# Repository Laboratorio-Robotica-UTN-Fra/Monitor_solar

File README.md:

# Monitor Solar

Proyecto para mostrar los valores de tension y corriente de un sistema solar

## Folder Structure

- `code/` - Archivos de codigo para esp8266.
- `Componentes/` - Documentacion y archivos de simbolos para kicad.
- `img/` - Imagenes del proyecto
- `README.md` - Explicacion del proyecto.

## Getting Started

1. Clone the repository:
    ```bash
    git clone https://github.com/yourusername/Monitor_solar.git
    ```
2. Follow instructions in `docs/` to set up and run the project.

## License

See `LICENSE` for details.

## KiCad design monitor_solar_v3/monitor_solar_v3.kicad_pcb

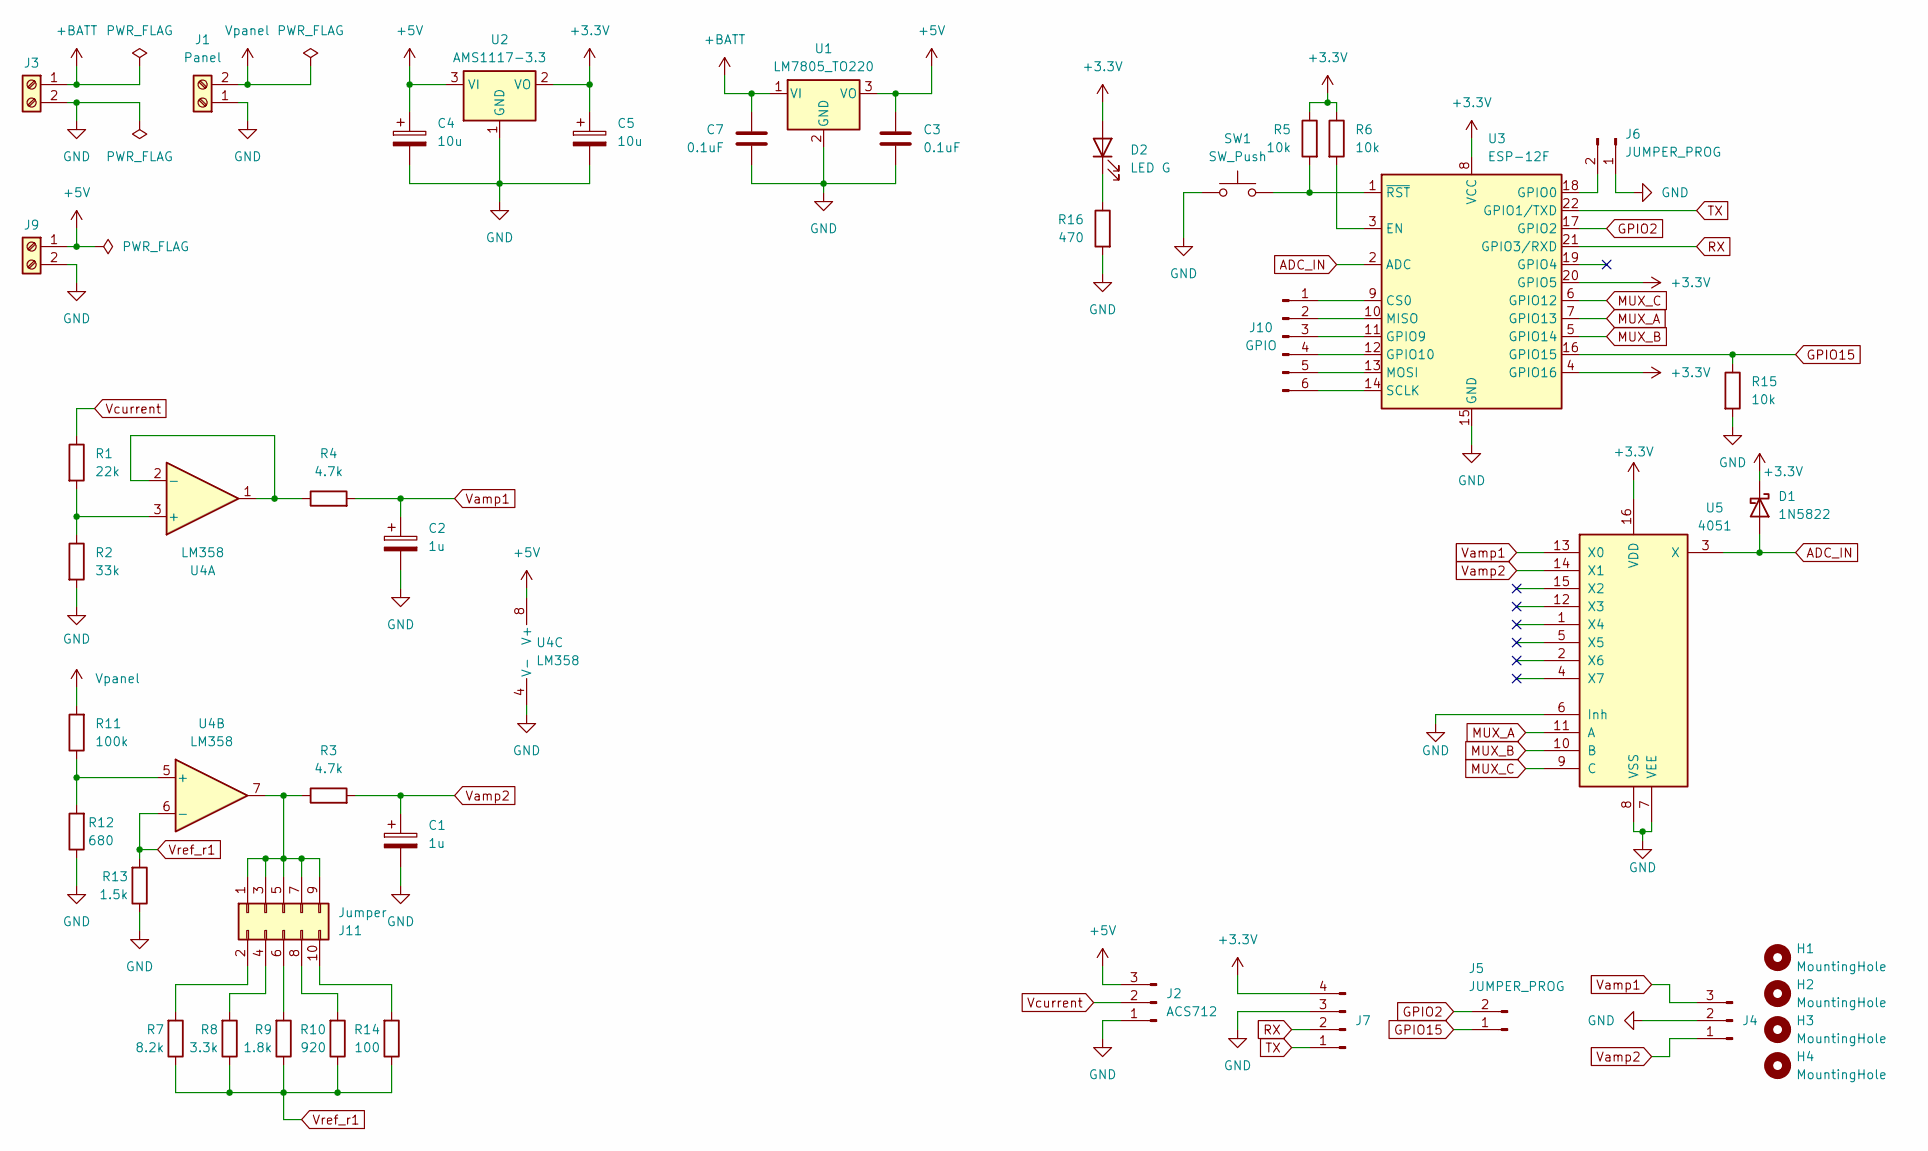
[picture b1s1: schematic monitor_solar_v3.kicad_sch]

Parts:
C1, C2: 1u; CP_Radial_D5.0mm_P2.50mm
C3, C7: 0.1uF; C_Disc_D3.0mm_W2.0mm_P2.50mm
C4, C5: 10u; CP_Radial_D5.0mm_P2.50mm
D1: 1N5822; D_DO-201AD_P15.24mm_Horizontal
D2: LED G; LED_D3.0mm
H1, H2, H3, H4: MountingHole; MountingHole_3.2mm_M3
J1: Panel; TerminalBlock_Phoenix_MKDS-1,5-2-5.08_1x02_P5.08mm_Horizont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
J2: ACS712; PinHeader_1x03_P2.54mm_Vertical
J3: Battery; TerminalBlock_Phoenix_MKDS-1,5-2-5.08_1x02_P5.08mm_Horizont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
J4: AMP_OUT; PinHeader_1x03_P2.54mm_Vertical
J5, J6: JUMPER_PROG; PinHeader_1x02_P2.54mm_Vertical
J7: PROGRAM; PinHeader_1x04_P2.54mm_Vertical
J9: Reg 5V; TerminalBlock_Phoenix_MKDS-1,5-2-5.08_1x02_P5.08mm_Horizont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
J10: GPIO; PinHeader_1x06_P2.54mm_Vertical
J11: Jumper; PinHeader_2x05_P2.54mm_Vertical
R1: 22k; R_Axial_DIN0207_L6.3mm_D2.5mm_P10.16mm_Horizontal
R2: 33k; R_Axial_DIN0207_L6.3mm_D2.5mm_P10.16mm_Horizontal
R3: 4.7k; R_Axial_DIN0207_L6.3mm_D2.5mm_P10.16mm_Horizontal
R4: 4.7k; R_Axial_DIN0207_L6.3mm_D2.5mm_P7.62mm_Horizontal
R5, R6, R15: 10k; R_Axial_DIN0207_L6.3mm_D2.5mm_P10.16mm_Horizontal
R7: 8.2k; R_Axial_DIN0207_L6.3mm_D2.5mm_P7.62mm_Horizontal
R8: 3.3k; R_Axial_DIN0207_L6.3mm_D2.5mm_P7.62mm_Horizontal
R9: 1.8k; R_Axial_DIN0207_L6.3mm_D2.5mm_P7.62mm_Horizontal
R10: 920; R_Axial_DIN0207_L6.3mm_D2.5mm_P7.62mm_Horizontal
R11: 100k; R_Axial_DIN0207_L6.3mm_D2.5mm_P10.16mm_Horizontal
R12: 680; R_Axial_DIN0207_L6.3mm_D2.5mm_P10.16mm_Horizontal
R13: 1.5k; R_Axial_DIN0207_L6.3mm_D2.5mm_P10.16mm_Horizontal
R14: 100; R_Axial_DIN0207_L6.3mm_D2.5mm_P7.62mm_Horizontal
R16: 470; R_Axial_DIN0207_L6.3mm_D2.5mm_P10.16mm_Horizontal
SW1: SW_Push; SW_PUSH_6mm
U1: LM7805_TO220; TO-220-3_Vertical
U2: AMS1117-3.3; SOT-223-3_TabPin2
U3: ESP-12F; ESP-12E
U4: LM358; DIP-8_W10.16mm_LongPads
U5: 4051; DIP-16_W7.62mm_Socket_LongPads

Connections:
+3.3V: C5.1, D1.1 (K), D2.2 (A), J7.4, R5.1, R6.1, U2.2 (VO), U3.4 (GPIO16), U3.8 (VCC), U3.20 (GPIO5), U5.16 (VDD)
+5V: C3.1, C4.1, J2.3, J9.1, U1.3 (VO), U2.3 (VI), U4.8 (V+)
+BATT: C7.1, J3.1, U1.1 (VI)
ADC_IN: D1.2 (A), U3.2 (ADC), U5.3 (X)
GND: C1.2, C2.2, C3.2, C4.2, C5.2, C7.2, J1.1, J2.1, J3.2, J4.2, J6.1, J7.3, J9.2, R2.2, R12.1, R13.1, R15.2, R16.2, SW1.1, U1.2 (GND), U2.1 (GND), U3.15 (GND), U4.4 (V-), U5.6 (Inh), U5.7 (VEE), U5.8 (VSS)
GPIO2: J5.2, U3.17 (GPIO2)
GPIO15: J5.1, R15.1, U3.16 (GPIO15)
MUX_A: U3.7 (GPIO13), U5.11 (A)
MUX_B: U3.5 (GPIO14), U5.10 (B)
MUX_C: U3.6 (GPIO12), U5.9 (C)
unnamed: D2.1 (K), R16.1
unnamed: J6.2, U3.18 (GPIO0)
unnamed: J10.1, U3.9 (CS0)
unnamed: J10.2, U3.10 (MISO)
unnamed: J10.3, U3.11 (GPIO9)
unnamed: J10.4, U3.12 (GPIO10)
unnamed: J10.5, U3.13 (MOSI)
unnamed: J10.6, U3.14 (SCLK)
unnamed: J11.1, J11.3, J11.5, J11.7, J11.9, R3.1, U4.7
unnamed: J11.2, R7.2
unnamed: J11.4, R8.2
unnamed: J11.6, R9.2
unnamed: J11.8, R10.2
unnamed: J11.10, R14.2
unnamed: R6.2, U3.3 (EN)
unnamed: R5.2, SW1.2, U3.1 (~RST)
unnamed: R1.2, R2.1, U4.3 (+)
unnamed: R4.1, U4.1, U4.2 (-)
unnamed: R11.1, R12.2, U4.5 (+)
RX: J7.2, U3.21 (GPIO3/RXD)
TX: J7.1, U3.22 (GPIO1/TXD)
Vamp1: C2.1, J4.3, R4.2, U5.13 (X0)
Vamp2: C1.1, J4.1, R3.2, U5.14 (X1)
Vcurrent: J2.2, R1.1
Vpanel: J1.2, R11.2
Vref_r1: R7.1, R8.1, R9.1, R10.1, R13.2, R14.1, U4.6 (-)

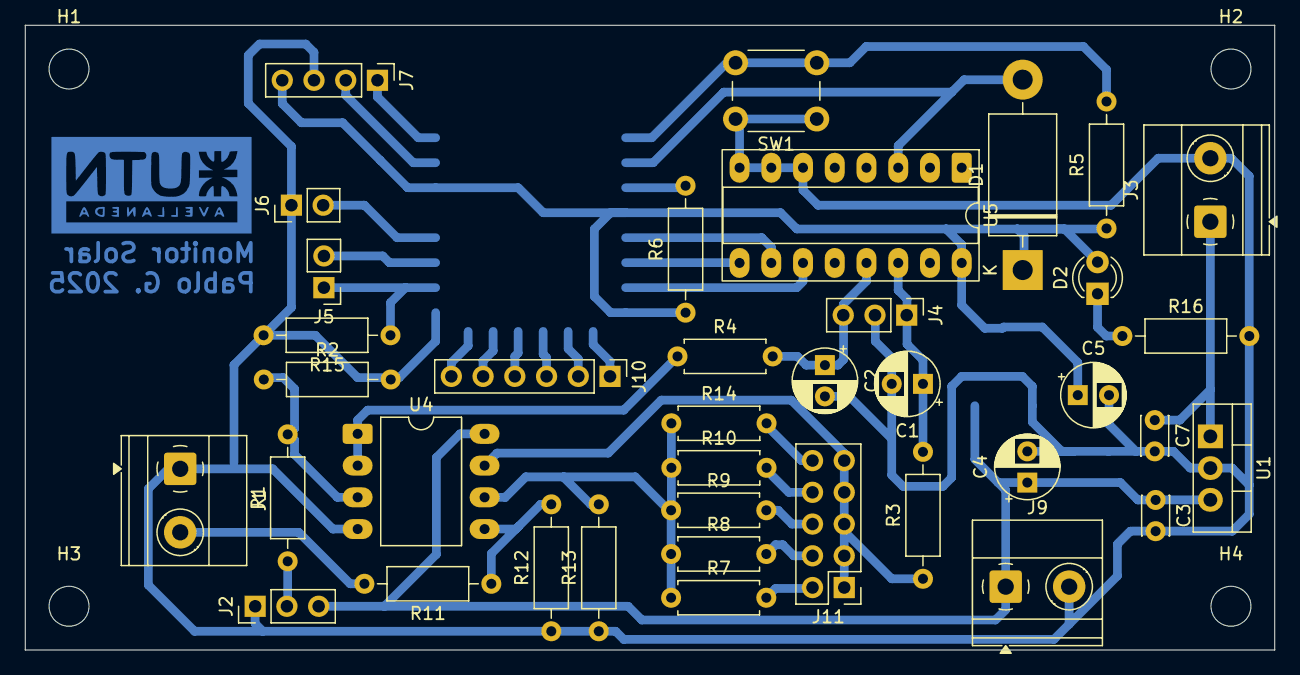
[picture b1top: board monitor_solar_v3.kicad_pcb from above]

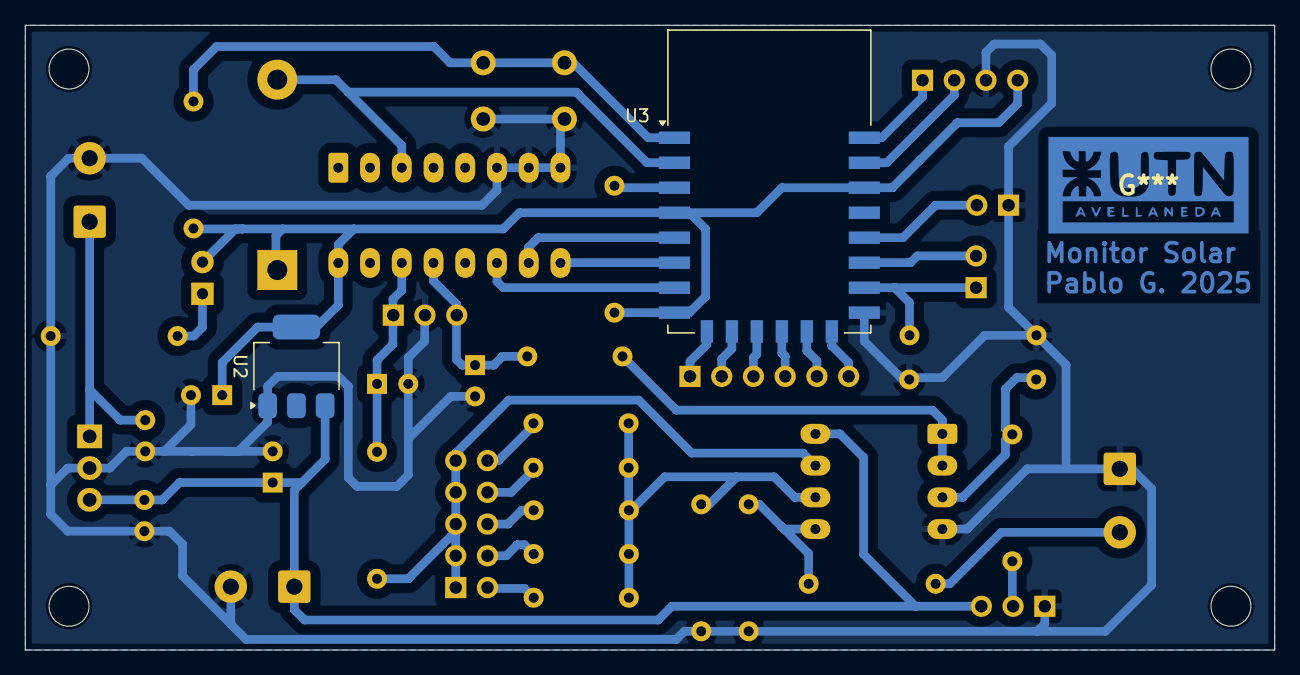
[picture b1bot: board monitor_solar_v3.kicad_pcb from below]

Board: 2 copper layers, 100.0 x 50.0 mm, 44 parts (2 on the bottom side), 36 nets.

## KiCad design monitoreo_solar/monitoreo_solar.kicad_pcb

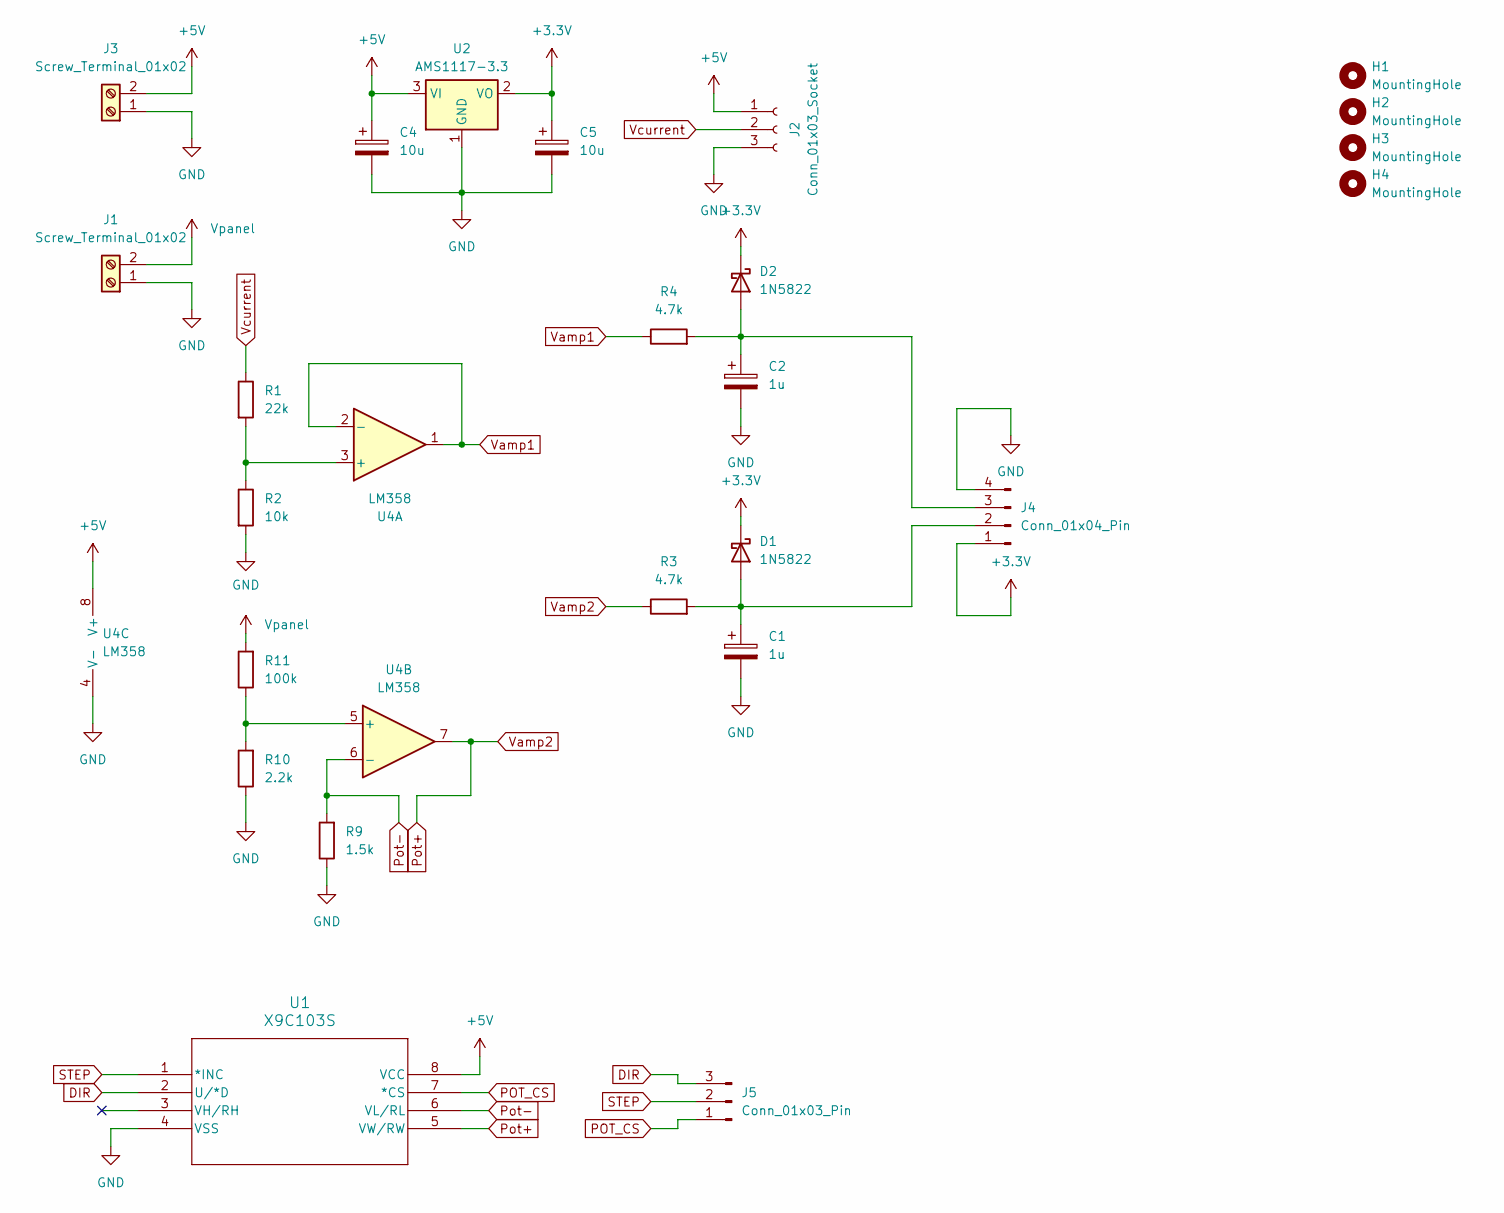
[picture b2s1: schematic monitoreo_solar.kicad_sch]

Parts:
C1, C2: 1u; CP_Radial_D5.0mm_P2.50mm
C4, C5: 10u; CP_Radial_D5.0mm_P2.50mm
D1, D2: 1N5822; D_DO-201AD_P15.24mm_Horizontal
H1, H2, H3, H4: MountingHole; MountingHole_3.2mm_M3
J1, J3: Screw_Terminal_01x02; TerminalBlock_Phoenix_MKDS-1,5-2_1x02_P5.00mm_Horizontal
J2: Conn_01x03_Socket; PinHeader_1x03_P2.54mm_Vertical
J4: Conn_01x04_Pin; PinHeader_1x04_P2.54mm_Vertical
J5: Conn_01x03_Pin; PinHeader_1x03_P2.54mm_Vertical
R1: 22k; R_Axial_DIN0207_L6.3mm_D2.5mm_P10.16mm_Horizontal
R2: 10k; R_Axial_DIN0207_L6.3mm_D2.5mm_P10.16mm_Horizontal
R3, R4: 4.7k; R_Axial_DIN0207_L6.3mm_D2.5mm_P10.16mm_Horizontal
R9: 1.5k; R_Axial_DIN0207_L6.3mm_D2.5mm_P10.16mm_Horizontal
R10: 2.2k; R_Axial_DIN0207_L6.3mm_D2.5mm_P10.16mm_Horizontal
R11: 100k; R_Axial_DIN0207_L6.3mm_D2.5mm_P10.16mm_Horizontal
U1: X9C103S; SOIC8_3P9116X4P9022_INR
U2: AMS1117-3.3; TO-220-3_Vertical
U4: LM358; DIP-8_W10.16mm_LongPads

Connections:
+3.3V: C5.1, D1.1 (K), D2.1 (K), J4.1, U2.2 (VO)
+5V: C4.1, J2.1, J3.2, U1.8 (VCC), U2.3 (VI), U4.8 (V+)
DIR: J5.3, U1.2 (U/*D)
GND: C1.2, C2.2, C4.2, C5.2, J1.1, J2.3, J3.1, J4.4, R2.2, R9.1, R10.1, U1.4 (VSS), U2.1 (GND), U4.4 (V-)
unnamed: C1.1, D1.2 (A), J4.2, R3.2
unnamed: C2.1, D2.2 (A), J4.3, R4.2
unnamed: R1.2, R2.1, U4.3 (+)
unnamed: R10.2, R11.1, U4.5 (+)
POT_CS: J5.1, U1.7 (*CS)
Pot+: R3.1, U1.5 (VW/RW), U4.7
Pot-: R9.2, U1.6 (VL/RL), U4.6 (-)
STEP: J5.2, U1.1 (*INC)
Vamp1: R4.1, U4.1, U4.2 (-)
Vcurrent: J2.2, R1.1
Vpanel: J1.2, R11.2

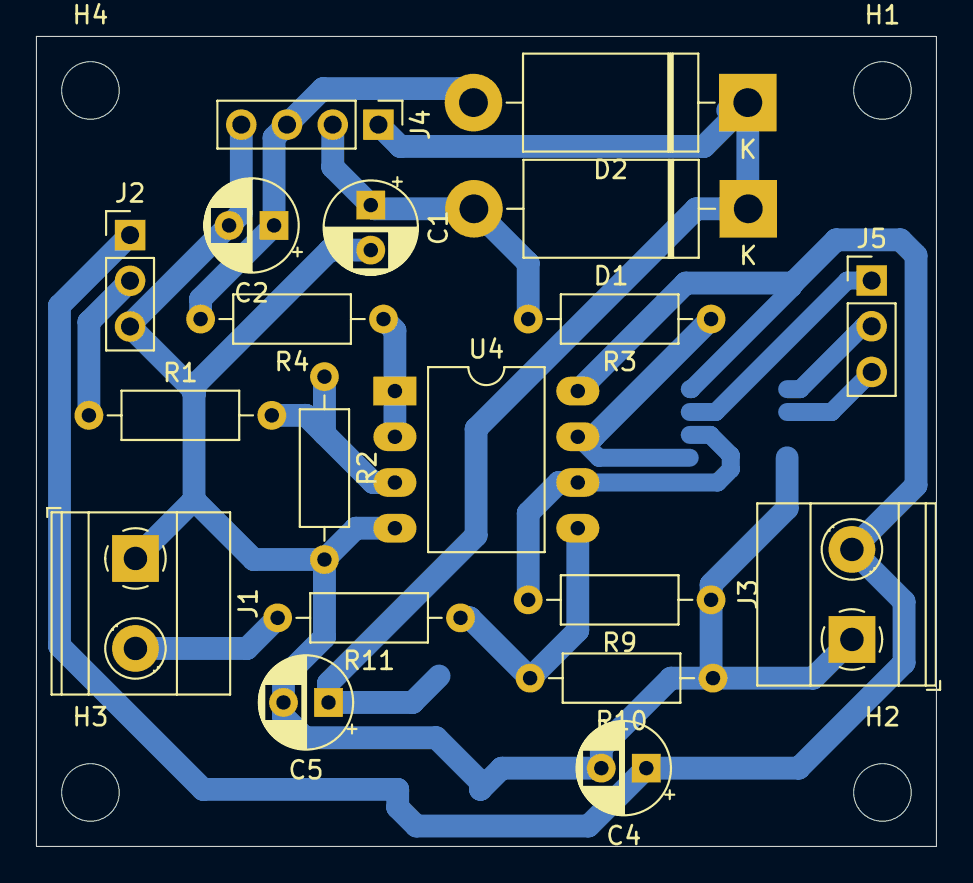
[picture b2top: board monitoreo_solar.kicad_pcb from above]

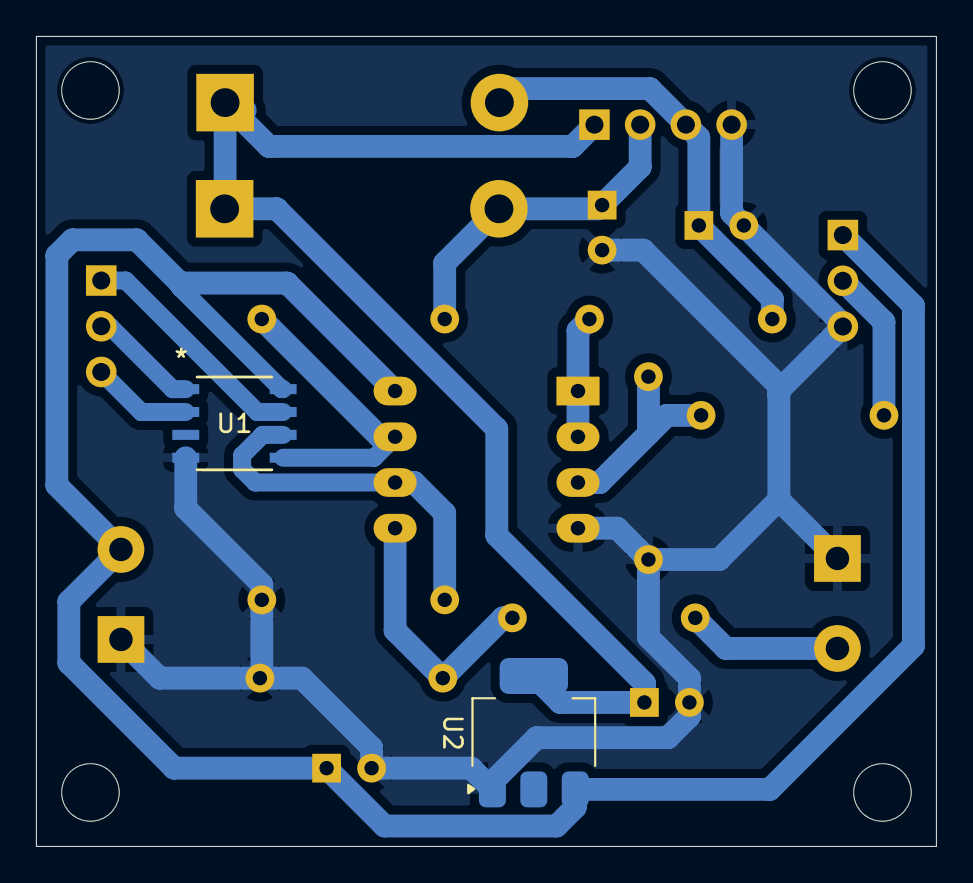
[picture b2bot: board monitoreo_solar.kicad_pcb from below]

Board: 2 copper layers, 50.0 x 45.0 mm, 25 parts (2 on the bottom side), 15 nets.

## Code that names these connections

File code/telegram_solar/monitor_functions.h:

#ifndef __MONITOR_FUNCTIONS__
#define __MONITOR_FUNCTIONS__

#include "Arduino.h"
#include <NTPClient.h>
#include <WiFiUdp.h>

#define GPIO_MUX_A  13
#define GPIO_MUX_B  14
#define GPIO_MUX_C  12

#define GPIO_RELAY_1  10
#define GPIO_RELAY_2  2

#define ADC_RESOLUTION 1024
#define ADC_VREF 1.0f
#define ADC_BITS2VOLTS ((float) (ADC_VREF / ADC_RESOLUTION))


// 2.2 * (1 + 3.3 / 1.5) / 102.2 = 0.068845 => ^-1 = 14.517
#define ADC_V_GAIN 100680.0 / 680
#define PANEL_V_OFFSET 0.6f
// Resistencias = ((33k + 20k) / 33k)
// Inversa de la pendiente sensor ACS712
// 52k // 100k => 0.342 ~ 0.35
// 0A -> 2.52v -> 0.88v     | 0 v
// 30A -> 0.55v -> 0.19v    | 0.69 v
#define ACS712_OFFSET_COUNTS 934
#define ACS712_SENSITIVITY 42.47f 


WiFiUDP ntpUDP;
NTPClient timeClient(ntpUDP, "pool.ntp.org", -3 * 3600, 60000);

enum sensor_type{
    VOLTAGE,
    CURRENT
};

void select_sensor(enum sensor_type tipo);
struct PanelData {
    float voltage;
    float current;
    float power;
    float energy;
    String date_time;
};

void solar_gpio_init(void) {
    pinMode(GPIO_MUX_A, OUTPUT);
    pinMode(GPIO_MUX_B, OUTPUT);
    pinMode(GPIO_MUX_C, OUTPUT);
    select_sensor(VOLTAGE);
    
    pinMode(GPIO_RELAY_1, OUTPUT);
    pinMode(GPIO_RELAY_2, OUTPUT);
    digitalWrite(GPIO_RELAY_1, HIGH);
    digitalWrite(GPIO_RELAY_2, HIGH);
}

float get_voltage_value(int r1_value) {
    float gain =  ADC_V_GAIN / (1 + r1_value / 1500.0);
    return gain * analogRead(A0) * ADC_BITS2VOLTS - PANEL_V_OFFSET;
}

float get_current_value() {
    float adc_i_volts =  ACS712_SENSITIVITY * (ACS712_OFFSET_COUNTS - analogRead(A0)) * ADC_BITS2VOLTS;
    return adc_i_volts; // - 0.878
}


void select_sensor(enum sensor_type tipo) {
    switch (tipo) {
        case VOLTAGE:
            digitalWrite(GPIO_MUX_A, LOW);
            digitalWrite(GPIO_MUX_B, HIGH);
            digitalWrite(GPIO_MUX_C, LOW);
            break;
        case CURRENT:
            digitalWrite(GPIO_MUX_A, HIGH);
            digitalWrite(GPIO_MUX_B, HIGH);
            digitalWrite(GPIO_MUX_C, LOW);
            break;
    }
    delay(50);
}

void print_panel_data(PanelData panel_data) {
    Serial.println("Voltage: " + String(panel_data.voltage) + "V");
    Serial.println("Current: " + String(panel_data.current) + "A");
    Serial.println("Power: " + String(panel_data.power) + "W");
    Serial.println("Energy: " + String(panel_data.energy) + "kWh");
    Serial.println("Date/Time: " + panel_data.date_time);
}

PanelData get_panel_data(unsigned long last_reading_time) {
    PanelData panel_data;
    panel_data.voltage = get_voltage_value(3300);
    panel_data.current = get_current_value();
    panel_data.power = panel_data.voltage * panel_data.current;
    panel_data.energy += panel_data.power * (millis() - last_reading_time) / 3600000.0; // kWh
    timeClient.update();
    panel_data.date_time = timeClient.getFormattedTime();
    
    print_panel_data(panel_data);

    return panel_data;
}

#endif

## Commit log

2024-08-14 feat: add schematic and notebook with first values
2024-08-15 first pcb design
2024-10-01 feat: v2 pcb con board potenciometro a medida
2024-10-02 Test Flatcam
    Prueba para utilizar flatcam a partir de la pcb v2
2025-03-07 Cambios menores
2025-03-14 Adding ESP-12 and new pcb
2025-03-18 PCB esp12 v1.0
2025-03-21 codigo v1: pruebas en telegram
2025-03-22 MUX, OpAmp and Relay tested
2025-03-26 PCB v3
2025-03-27 PCB V3 finished
2025-04-04 Add led for power status
2025-04-04 Cambios en el codigo para telegram y ajuste de resistencias del pcb
2025-04-12 Test ics712 value
2025-04-21 Extract credentials
2025-04-21 Cambios en la sensibilidad de los canales. Modificar valores de resistencias en esquematico
2025-05-16 add readme and images
2025-06-14 feat: all modules working
